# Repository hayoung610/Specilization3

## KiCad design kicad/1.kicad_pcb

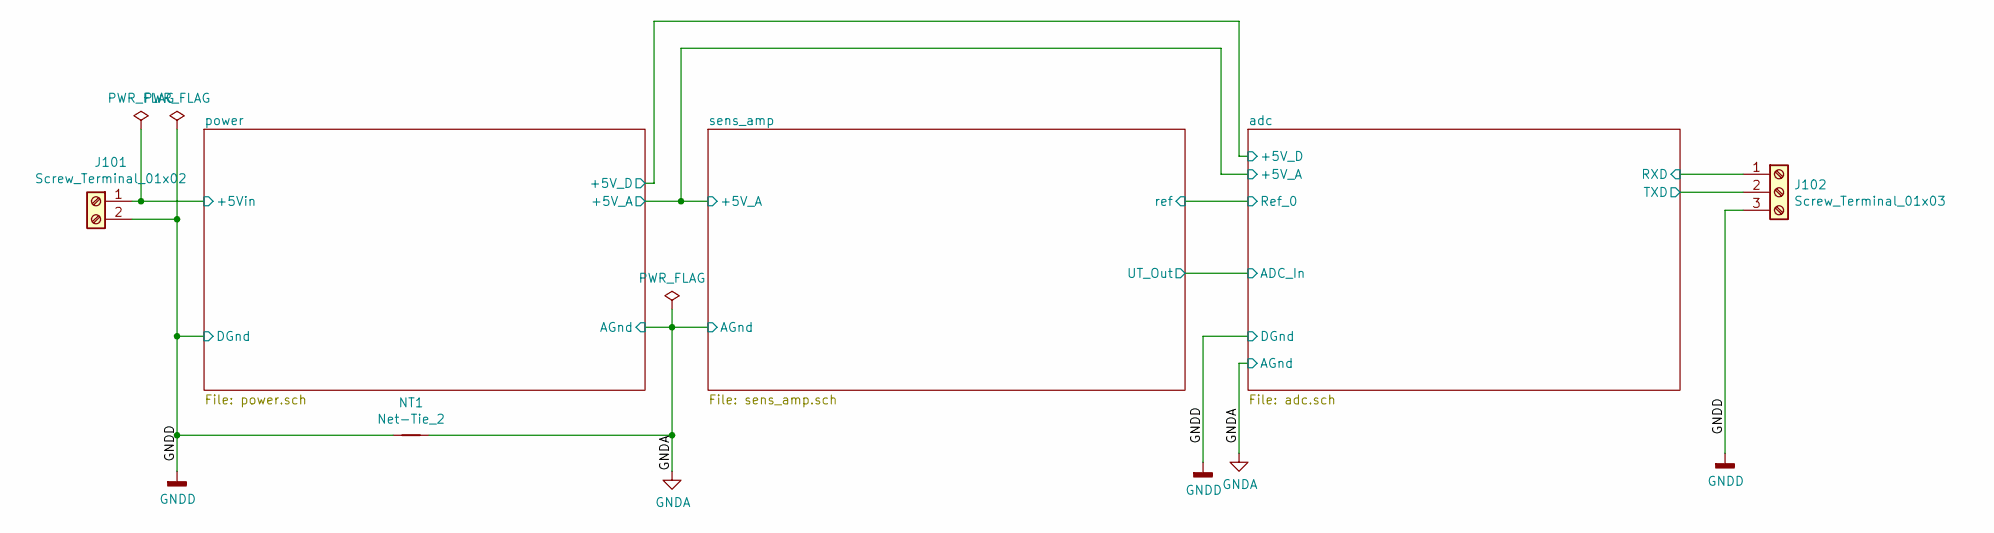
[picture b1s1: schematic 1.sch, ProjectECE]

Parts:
J101: Screw_Terminal_01x02; TerminalBlock_RND_205-00001_1x02_P5.00mm_Horizontal
J102: Screw_Terminal_01x03; TerminalBlock_RND_205-00002_1x03_P5.00mm_Horizontal
NT1: Net-Tie_2; NetTie-2_SMD_Pad2.0mm

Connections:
/adc/RXD: J102.1; also elsewhere on the board
/adc/TXD: J102.2; also elsewhere on the board
/power/+5Vin: J101.1; also elsewhere on the board
GNDA: NT1.2; also elsewhere on the board
GNDD: J101.2, J102.3, NT1.1; also elsewhere on the board

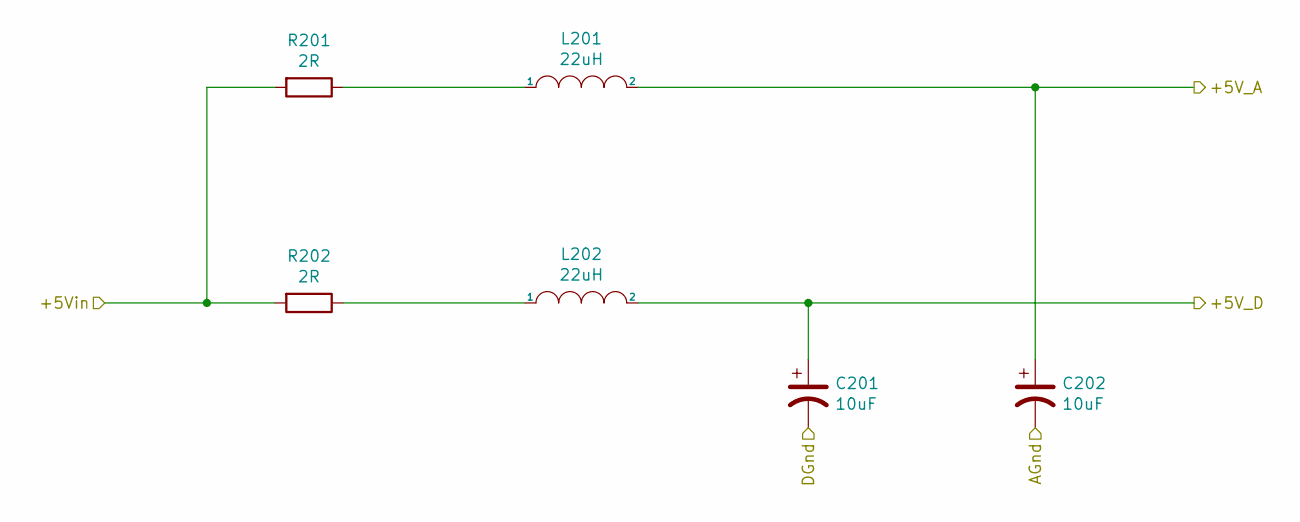
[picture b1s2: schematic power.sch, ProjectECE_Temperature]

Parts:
C201, C202: 10uF; CP_EIA-3216-18_Kemet-A
L201, L202: 22uH; L_1210_3225Metric
R201, R202: 2R; R_0805_2012Metric_Pad1.15x1.40mm_HandSolder

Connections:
/adc/+5V_A: C202.1, L201.2; also elsewhere on the board
/adc/+5V_D: C201.1, L202.2; also elsewhere on the board
/power/+5Vin: R201.2, R202.2; also elsewhere on the board
GNDA: C202.2; also elsewhere on the board
GNDD: C201.2; also elsewhere on the board
unnamed: L201.1, R201.1
unnamed: L202.1, R202.1

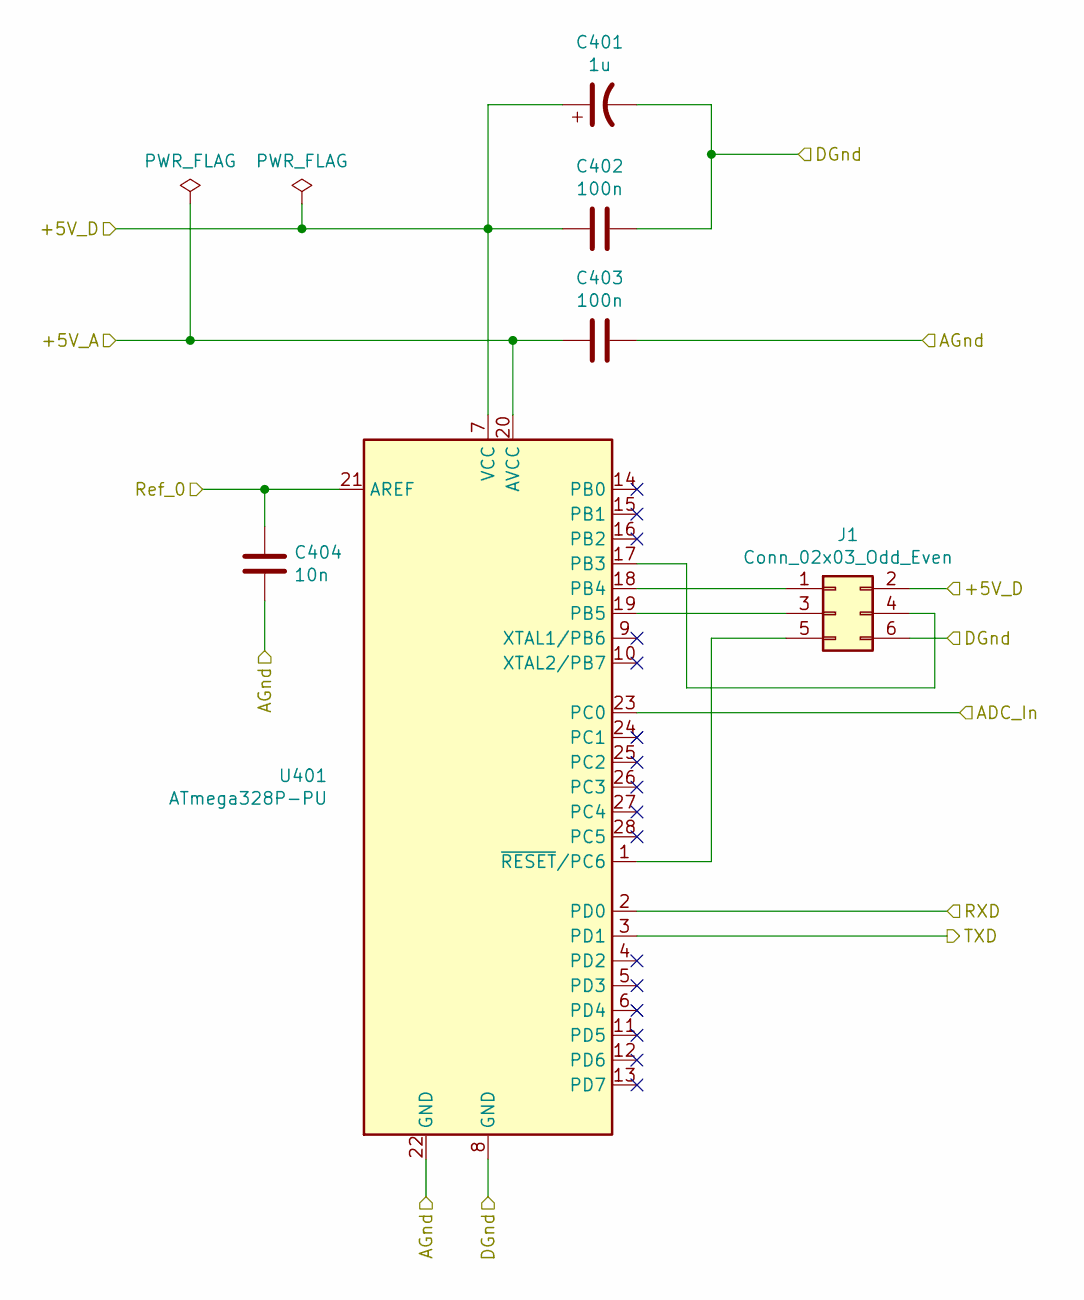
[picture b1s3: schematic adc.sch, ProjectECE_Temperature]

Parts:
C401: 1u; CP_EIA-3216-18_Kemet-A
C402, C403: 100n; C_0805_2012Metric_Pad1.15x1.40mm_HandSolder
C404: 10n; C_0805_2012Metric_Pad1.15x1.40mm_HandSolder
J1: Conn_02x03_Odd_Even; PinHeader_2x03_P2.54mm_Vertical
U401: ATmega328P-PU; DIP-28_W7.62mm

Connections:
/adc/+5V_A: C403.2, U401.20 (AVCC); also elsewhere on the board
/adc/+5V_D: C401.1, C402.2, J1.2, U401.7 (VCC); also elsewhere on the board
/adc/ADC_In: U401.23 (PC0); also elsewhere on the board
/adc/RXD: U401.2 (PD0); also elsewhere on the board
/adc/Ref_0: C404.1, U401.21 (AREF); also elsewhere on the board
/adc/TXD: U401.3 (PD1); also elsewhere on the board
GNDA: C403.1, C404.2, U401.22 (GND); also elsewhere on the board
GNDD: C401.2, C402.1, J1.6, U401.8 (GND); also elsewhere on the board
unnamed: J1.1, U401.18 (PB4)
unnamed: J1.3, U401.19 (PB5)
unnamed: J1.4, U401.17 (PB3)
unnamed: J1.5, U401.1 (~RESET~/PC6)

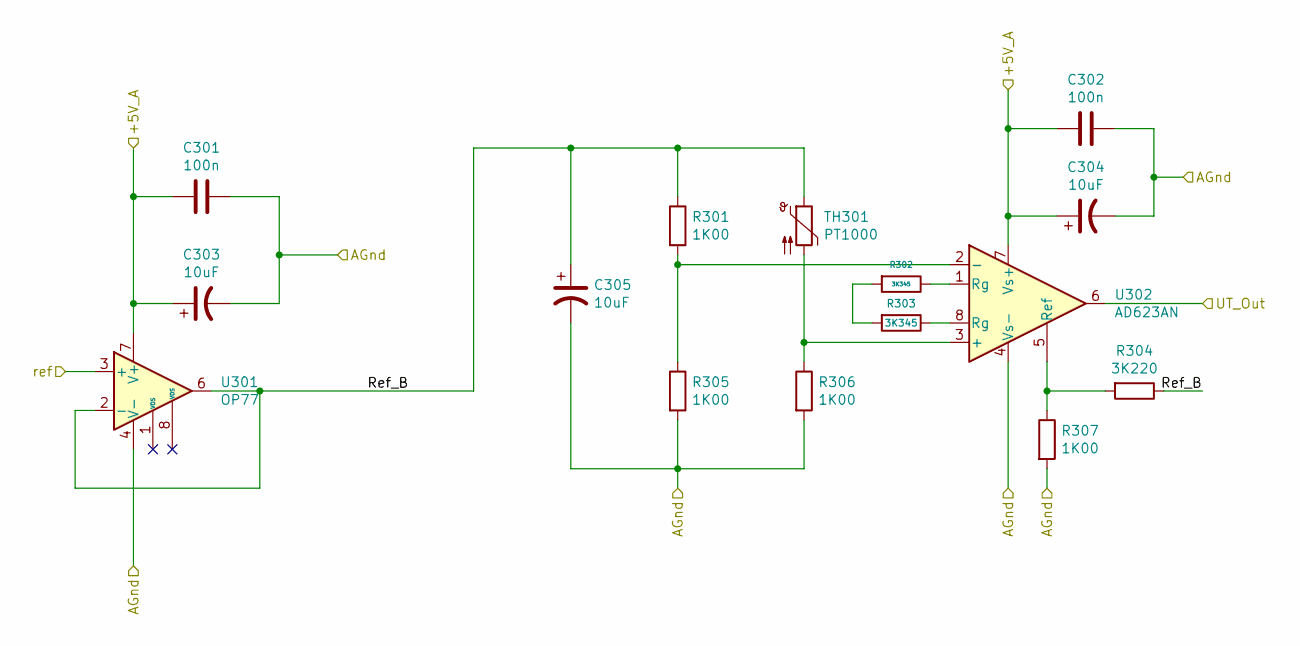
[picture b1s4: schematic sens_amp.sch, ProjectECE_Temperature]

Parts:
C301, C302: 100n; C_0805_2012Metric_Pad1.15x1.40mm_HandSolder
C303, C304, C305: 10uF; CP_EIA-3216-18_Kemet-A
R301, R305, R306, R307: 1K00; R_0805_2012Metric_Pad1.15x1.40mm_HandSolder
R302, R303: 3K345; R_0805_2012Metric_Pad1.15x1.40mm_HandSolder
R304: 3K220; R_0805_2012Metric_Pad1.15x1.40mm_HandSolder
TH301: PT1000; R_0805_2012Metric_Pad1.15x1.40mm_HandSolder
U301: OP77; DIP-8_W7.62mm
U302: AD623AN; DIP-8_W7.62mm

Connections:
/adc/+5V_A: C301.2, C302.2, C303.1, C304.1, U301.7 (V+), U302.7 (Vs+); also elsewhere on the board
/adc/ADC_In: U302.6; also elsewhere on the board
/adc/Ref_0: U301.3 (+); also elsewhere on the board
/sens_amp/Ref_B: C305.1, R301.1, R304.1, TH301.1, U301.2 (-), U301.6
GNDA: C301.1, C302.1, C303.2, C304.2, C305.2, R305.2, R306.2, R307.2, U301.4 (V-), U302.4 (Vs-); also elsewhere on the board
unnamed: R301.2, R305.1, U302.2 (-)
unnamed: R302.1, U302.1 (Rg)
unnamed: R302.2, R303.2
unnamed: R303.1, U302.8 (Rg)
unnamed: R304.2, R307.1, U302.5 (Ref)
unnamed: R306.1, TH301.2, U302.3 (+)

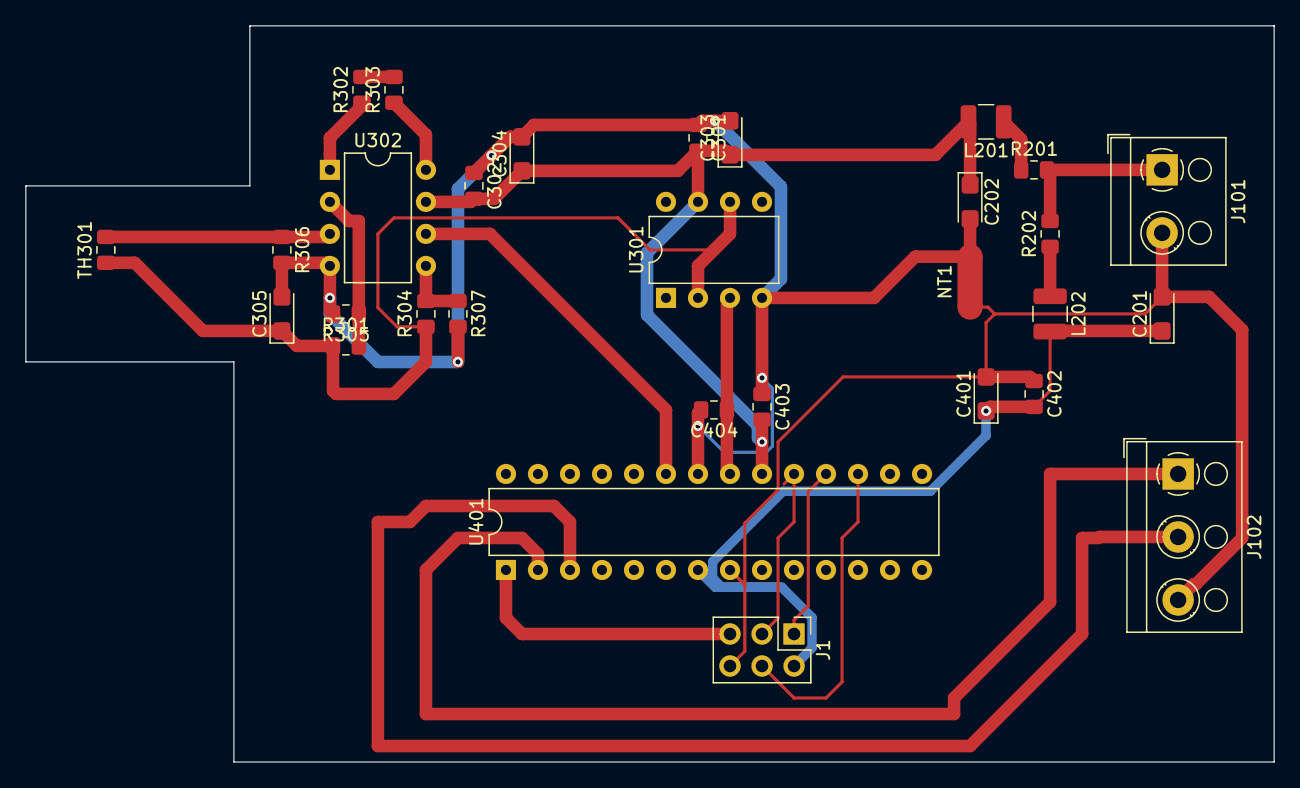
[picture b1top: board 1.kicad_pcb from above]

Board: 2 copper layers, 99.1 x 58.4 mm, 30 parts (0 on the bottom side), 22 nets.
